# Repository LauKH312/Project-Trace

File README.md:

# Project Trace
Multimeter-oscilloscope made for the DTU Bsc. Introductory Project

## Project Structure
```txt
project-root/
│
├── hardware/              # KiCad
│   ├── boards/
│   │   └── main_board/
│   ├── libraries/
│   │   ├── symbols/
│   │   ├── footprints/
│   │   └── 3dmodels/
│   └── fabrication/
│
├── firmware/
│   └── trace-cube/
│
├── docs/
│   ├── architecture/
│   ├── hardware/
│   ├── firmware/
│   ├── manufacturing/
│   └── user_manual/
│
├── scripts/               # build + automation tools
├── tools/                 # dev utilities (flashers, converters)
│
├── .gitignore
├── README.md
└── VERSION
```

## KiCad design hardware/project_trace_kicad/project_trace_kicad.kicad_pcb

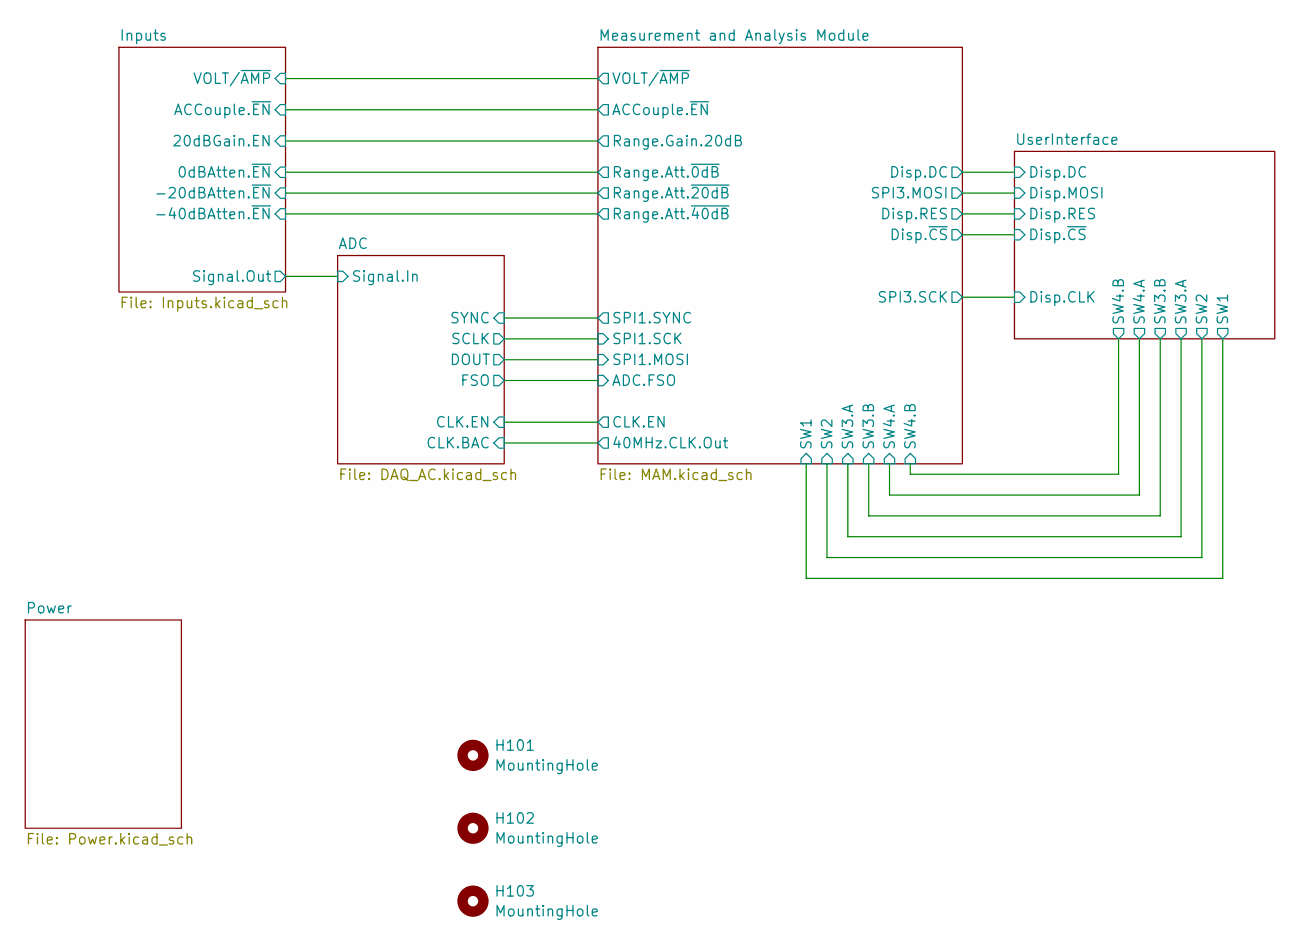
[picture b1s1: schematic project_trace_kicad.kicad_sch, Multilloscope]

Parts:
H101, H102, H103: MountingHole; MountingHole_4.3mm_M4_DIN965; DigikeyPN N/A

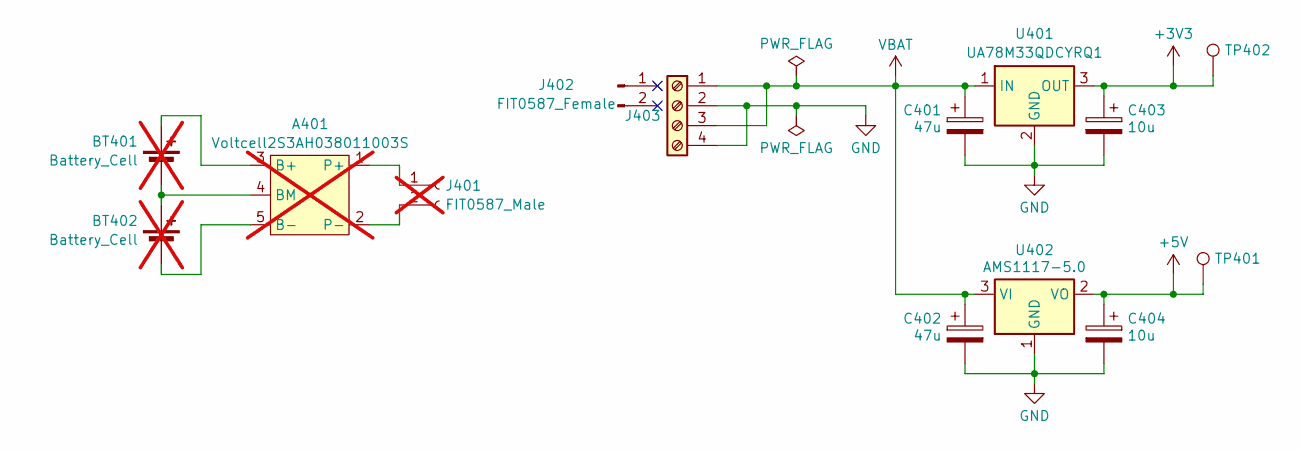
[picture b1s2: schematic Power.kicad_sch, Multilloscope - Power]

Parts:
A401: Voltcell2S3AH038011003S; DigikeyPN N/A; not fitted
BT401, BT402: Battery_Cell; DigikeyPN N/A; not fitted
C401, C402: 47u; CP_Radial_D6.3mm_P2.50mm; DigikeyPN N/A
C403, C404: 10u; CP_Radial_D6.3mm_P2.50mm; DigikeyPN N/A
J401: FIT0587_Male; DigikeyPN N/A; not fitted
J402: FIT0587_Female; DigikeyPN N/A
J403: Screw_Terminal_01x04; 691210910004; DigikeyPN 732-691210910004-ND
TP401, TP402: TestPoint; TestPoint_Pad_1.5x1.5mm; DigikeyPN N/A
U401: UA78M33QDCYRQ1; SOT-223-3_TabPin2; DigikeyPN 296-13424-1-ND
U402: AMS1117-5.0; SOT-223-3_TabPin2; DigikeyPN 5272-AMS1117-5.0CT-ND

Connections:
+3V3: C403.1, TP402.1 (1_1), U401.3 (OUT); also elsewhere on the board
+5V: C404.1, TP401.1 (1_1), U402.2 (VO); also elsewhere on the board
GND: C401.2, C402.2, C403.2, C404.2, J403.2, J403.4, U401.2 (GND), U402.1 (GND); also elsewhere on the board
unnamed: A401.1 (P+), J401.1
unnamed: A401.2 (P-), J401.2
unnamed: A401.3 (B+), BT401.1 (+)
unnamed: A401.4 (BM), BT401.2 (-), BT402.1 (+)
unnamed: A401.5 (B-), BT402.2 (-)
VBAT: C401.1, C402.1, J403.1, J403.3, U401.1 (IN), U402.3 (VI)

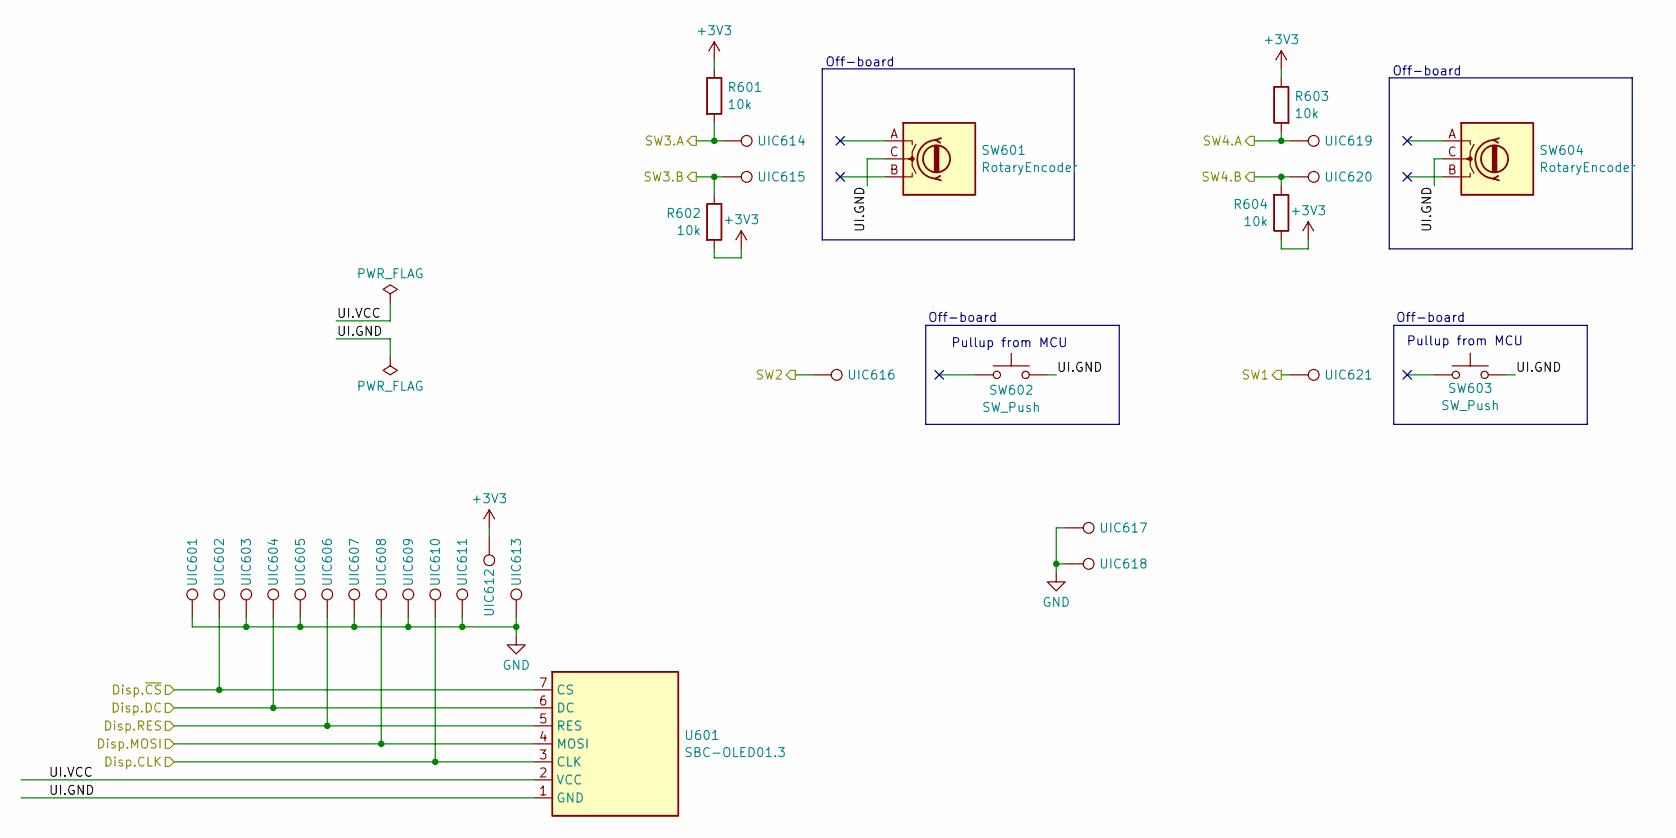
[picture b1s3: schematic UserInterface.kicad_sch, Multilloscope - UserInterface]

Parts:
R601, R602, R603, R604: 10k; R_0603_1608Metric_Pad0.98x0.95mm_HandSolder; DigikeyPN YAG1236CT-ND
SW601, SW604: RotaryEncoder; DigikeyPN N/A
SW602, SW603: SW_Push; DigikeyPN N/A
U601: SBC-OLED01.3; DigikeyPN N/A
UIC601, UIC602, UIC603, UIC604, UIC605, UIC606, UIC607, UIC608, UIC609, UIC610, UIC611, UIC612, UIC613, UIC614, UIC615, UIC616, UIC617, UIC618, UIC619, UIC620, UIC621: UIconnector; TestPoint_Pad_D2.5mm; DigikeyPN N/A

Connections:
+3V3: R601.1, R602.2, R603.1, R604.1, UIC612.1 (1_1); also elsewhere on the board
/Measurement and Analysis Module/Disp.DC: U601.6 (DC), UIC604.1 (1_1); also elsewhere on the board
/Measurement and Analysis Module/Disp.RES: U601.5 (RES), UIC606.1 (1_1); also elsewhere on the board
/Measurement and Analysis Module/Disp.~CS: U601.7 (CS), UIC602.1 (1_1); also elsewhere on the board
/Measurement and Analysis Module/SPI3.MOSI: U601.4 (MOSI), UIC608.1 (1_1); also elsewhere on the board
/Measurement and Analysis Module/SPI3.SCK: U601.3 (CLK), UIC610.1 (1_1); also elsewhere on the board
/Measurement and Analysis Module/SW1: UIC621.1 (1_1); also elsewhere on the board
/Measurement and Analysis Module/SW2: UIC616.1 (1_1); also elsewhere on the board
/Measurement and Analysis Module/SW3.A: R601.2, UIC614.1 (1_1); also elsewhere on the board
/Measurement and Analysis Module/SW3.B: R602.1, UIC615.1 (1_1); also elsewhere on the board
/Measurement and Analysis Module/SW4.A: R603.2, UIC619.1 (1_1); also elsewhere on the board
/Measurement and Analysis Module/SW4.B: R604.2, UIC620.1 (1_1); also elsewhere on the board
GND: UIC601.1 (1_1), UIC603.1 (1_1), UIC605.1 (1_1), UIC607.1 (1_1), UIC609.1 (1_1), UIC611.1 (1_1), UIC613.1 (1_1), UIC617.1 (1_1), UIC618.1 (1_1); also elsewhere on the board
unnamed: SW601.C, SW602.1, SW603.2, SW604.C, U601.1 (GND)

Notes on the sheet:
Pullup from MCU
Off-board

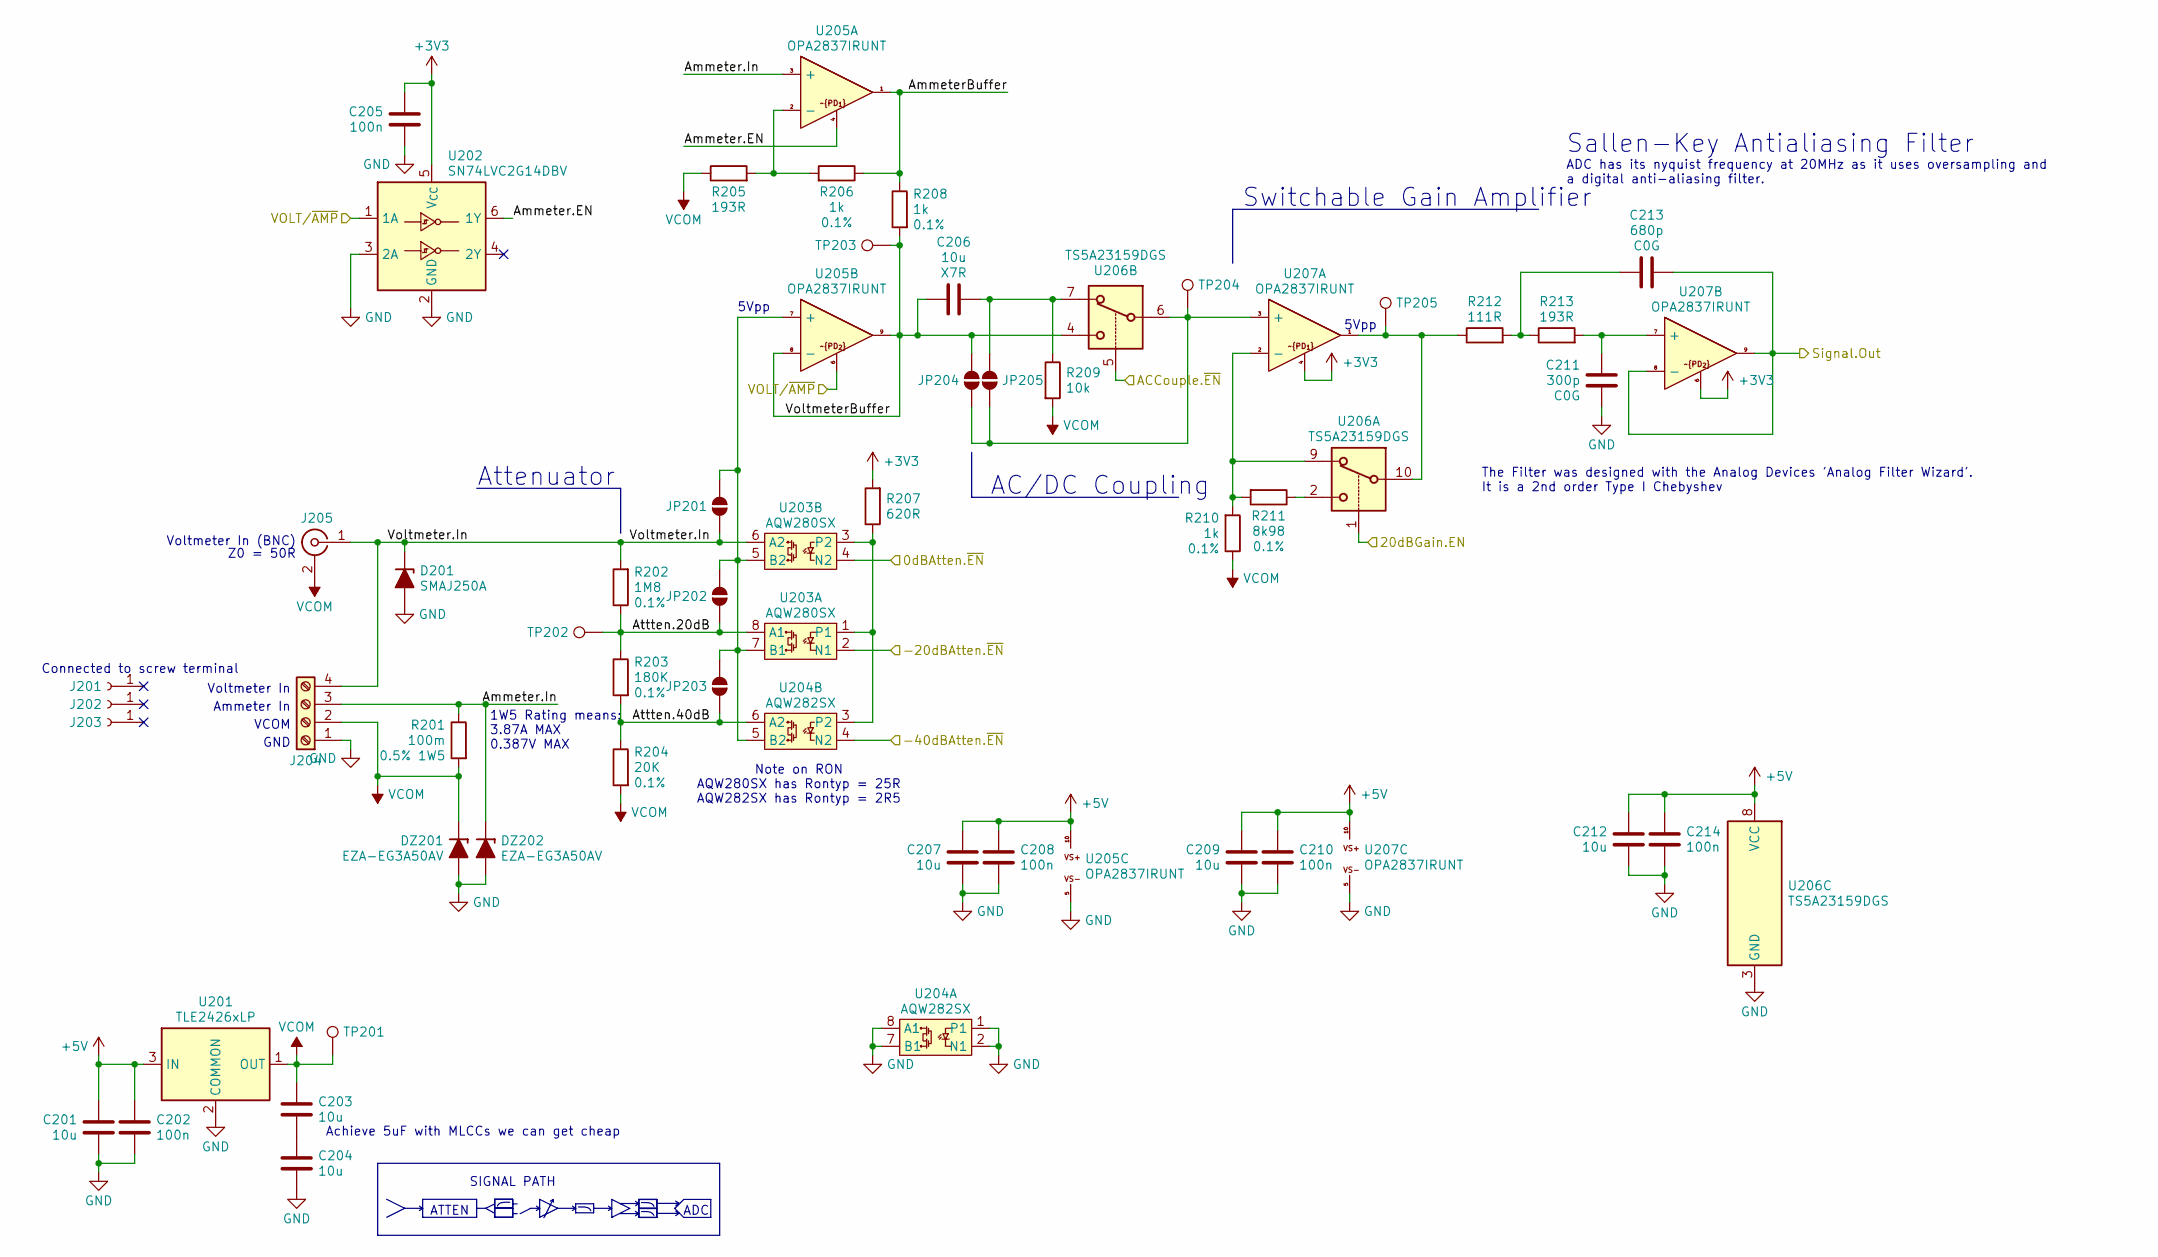
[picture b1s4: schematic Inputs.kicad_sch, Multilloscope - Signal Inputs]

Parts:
C201, C203, C204, C206, C207, C209, C212: 10u; C_0805_2012Metric_Pad1.18x1.45mm_HandSolder; DigikeyPN 490-10516-1-ND
C202, C205, C208, C210, C214: 100n; C_0603_1608Metric_Pad1.08x0.95mm_HandSolder; DigikeyPN 399-C0603C104K3RACTUCT-ND
C211: 300p; C_0603_1608Metric_Pad1.08x0.95mm_HandSolder; DigikeyPN 311-3967-1-ND
C213: 680p; C_0603_1608Metric_Pad1.08x0.95mm_HandSolder; DigikeyPN 311-1425-1-ND
D201: SMAJ250A; D_SMA_Handsoldering; DigikeyPN 13-SMAJ250A/TR13CT-ND
DZ201, DZ202: EZA-EG3A50AV; D_0603_1608Metric_Pad1.05x0.95mm_HandSolder; MouserPN 667-EZA-EG3A50AV
J201, J202, J203: Conn_01x01_Socket; DigikeyPN N/A
J204: Screw_Terminal_01x04; 691210910004; MouserPN 710-691210910004
J205: Conn_Coaxial; BNC_Female_0731385003; DigikeyPN WM14063-ND
JP201, JP202, JP203, JP204, JP205: SolderJumper_2_Open; SolderJumper-2_P1.3mm_Open_RoundedPad1.0x1.5mm; DigikeyPN N/A
R201: 100m; R_2512_6332Metric_Pad1.40x3.35mm_HandSolder; MouserPN SLW1TTER100D
R202: 1M8; R_0805_2012Metric_Pad1.20x1.40mm_HandSolder; DigikeyPN 408-2026-1-ND
R203: 180K; R_0603_1608Metric_Pad0.98x0.95mm_HandSolder; DigikeyPN YAG1548CT-ND
R204: 20K; R_0603_1608Metric_Pad0.98x0.95mm_HandSolder; DigikeyPN YAG1582CT-ND
R205, R213: 193R; R_0603_1608Metric_Pad0.98x0.95mm_HandSolder; DigikeyPN 13-RT0603DRE07193RLCT-ND
R206, R208, R210: 1k; R_0603_1608Metric_Pad0.98x0.95mm_HandSolder; DigikeyPN YAG1237CT-ND
R207: 620R; R_Axial_DIN0207_L6.3mm_D2.5mm_P10.16mm_Horizontal; DigikeyPN N/A
R209: 10k; R_0603_1608Metric_Pad0.98x0.95mm_HandSolder; DigikeyPN YAG1236CT-ND
R211: 8k98; R_0603_1608Metric_Pad0.98x0.95mm_HandSolder; DigikeyPN 13-RT0603BRD078K98LCT-ND
R212: 111R; R_0603_1608Metric_Pad0.98x0.95mm_HandSolder; DigikeyPN 2019-RN73R1JTTD1110B25CT-ND
TP201, TP202, TP203, TP204, TP205: TestPoint; TestPoint_Pad_1.5x1.5mm; DigikeyPN N/A
U201: TLE2426xLP; TO-92_Inline_Wide; DigikeyPN 296-TLE2426CLPRCT-ND
U202: SN74LVC2G14DBV; SOT-23-6_Handsoldering; DigikeyPN 296-13010-1-ND
U203: AQW280SX; AQW282SX; MouserPN 769-AQW280SX
U204: AQW282SX; DigikeyPN 255-AQW282SXCT-ND
U205, U207: OPA2837IRUNT; OPA2837IRUNT-Handsolder; DigikeyPN 296-53042-1-ND
U206: TS5A23159DGS; TSSOP-10_3x3mm_P0.5mm; DigikeyPN 296-18598-1-ND

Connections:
+3V3: C205.1, R207.2, U202.5 (V_{CC}), U207.4, U207.6; also elsewhere on the board
+5V: C201.2, C202.1, C207.2, C208.1, C209.2, C210.1, C212.2, C214.1, U201.3 (IN), U205.10, U206.8 (VCC), U207.10; also elsewhere on the board
/ADC/Signal.In: C213.2, U207.8 (-), U207.9; also elsewhere on the board
/Inputs/0dBAtten.~EN: U203.4 (N2); also elsewhere on the board
/Inputs/20dBGain.EN: U206.1; also elsewhere on the board
/Inputs/-20dBAtten.~EN: U203.2 (N1); also elsewhere on the board
/Inputs/-40dBAtten.~EN: U204.4 (N2); also elsewhere on the board
/Inputs/ACCouple.~EN: U206.5; also elsewhere on the board
/Inputs/Ammeter.EN: U202.6 (1Y), U205.4
/Inputs/Ammeter.In: DZ202.1 (K), J204.3, R201.1, U205.3 (+)
/Inputs/AmmeterBuffer: R206.1, R208.1, U205.1
/Inputs/Attten.20dB: JP202.1 (A), R202.1, R203.1, TP202.1 (1_1), U203.8 (A1)
/Inputs/Attten.40dB: JP203.1 (A), R203.2, R204.1, U204.6 (A2)
/Inputs/VOLT/~AMP: U202.1 (1A), U205.6; also elsewhere on the board
/Inputs/Voltmeter.In: D201.1 (K), J204.4, J205.1 (In), JP201.1 (A), R202.2, U203.6 (A2)
/Inputs/VoltmeterBuffer: C206.2, JP204.1 (A), R208.2, TP203.1 (1_1), U205.8 (-), U205.9, U206.4
GND: C201.1, C202.2, C204.1, C205.2, C207.1, C208.2, C209.1, C210.2, C211.1, C212.1, C214.2, D201.2 (A), DZ201.2 (A), DZ202.2 (A), J204.1, U201.2 (COMMON), U202.2 (GND), U202.3 (2A), U204.1, U204.2 (N1), U204.7 (B1), U204.8 (A1), U205.5, U206.3 (GND), U207.5; also elsewhere on the board
unnamed: C203.1, C204.2
unnamed: C213.1, R212.2, R213.1
unnamed: JP201.2 (B), JP202.2 (B), JP203.2 (B), U203.5 (B2), U203.7 (B1), U204.5 (B2), U205.7 (+)
unnamed: JP204.2 (B), JP205.2 (B), TP204.1 (1_1), U206.6, U207.3 (+)
unnamed: C206.1, JP205.1 (A), R209.1, U206.7
unnamed: R211.1, U206.2
unnamed: R212.1, TP205.1 (1_1), U206.10, U207.1
unnamed: R207.1, U203.1, U203.3 (P2), U204.3 (P2)
unnamed: R205.2, R206.2, U205.2 (-)
unnamed: R210.2, R211.2, U206.9, U207.2 (-)
unnamed: C211.2, R213.2, U207.7 (+)
VCOM: C203.2, DZ201.1 (K), J204.2, J205.2 (Ext), R201.2, R204.2, R205.1, R209.2, R210.1, TP201.1 (1_1), U201.1 (OUT); also elsewhere on the board

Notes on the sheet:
ADC has its nyquist frequency at 20MHz as it uses oversampling and a digital anti-aliasing filter.
GND
Voltmeter In
Attenuator
VCOM
The Filter was designed with the Analog Devices 'Analog Filter Wizard'. It is a 2nd order Type I Chebyshev
Achieve 5uF with MLCCs we can get cheap
Note on RON AQW280SX has Rontyp = 25R AQW282SX has Rontyp = 2R5
Z0 = 50R
ADC
ATTEN
5Vpp
1W5 Rating means: 3.87A MAX 0.387V MAX
Ammeter In
AC/DC Coupling
Switchable Gain Amplifier
SIGNAL PATH
Sallen-Key Antialiasing Filter
Connected to screw terminal
Voltmeter In (BNC)

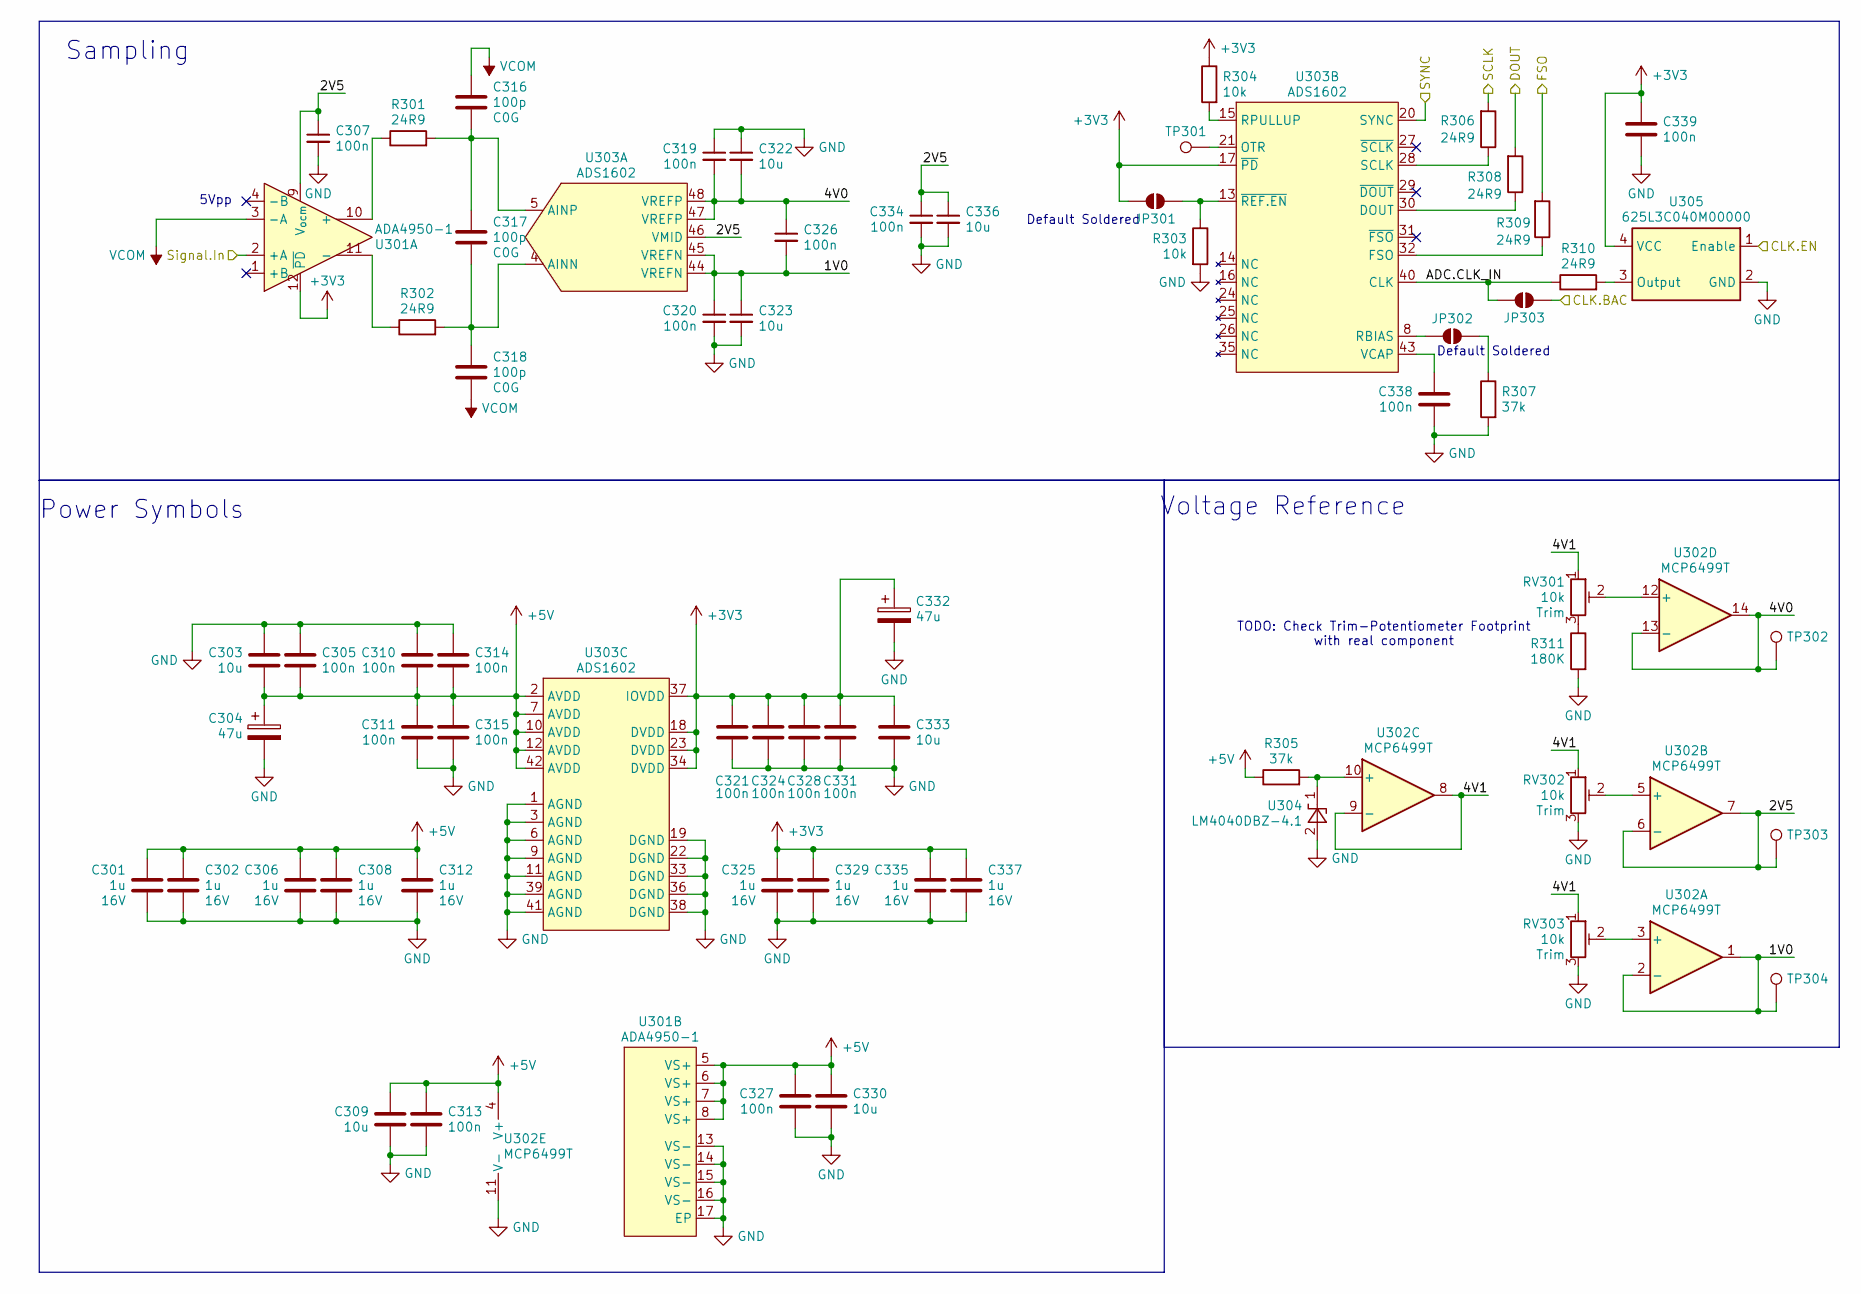
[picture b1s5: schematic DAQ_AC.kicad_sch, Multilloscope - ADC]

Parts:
C301, C302, C306, C308, C312, C325, C329, C335, C337: 1u; C_0603_1608Metric_Pad1.08x0.95mm_HandSolder; DigikeyPN 399-C0603C105K4RACTUCT-ND
C303, C309, C322, C323, C330, C333, C336: 10u; C_0805_2012Metric_Pad1.18x1.45mm_HandSolder; DigikeyPN 490-10516-1-ND
C304, C332: 47u; CP_Radial_D6.3mm_P2.50mm; DigikeyPN N/A
C305, C307, C310, C311, C313, C314, C315, C319, C320, C321, C324, C326, C327, C328, C331, C334, C338, C339: 100n; C_0603_1608Metric_Pad1.08x0.95mm_HandSolder; DigikeyPN 399-C0603C104K3RACTUCT-ND
C316, C317, C318: 100p; C_0603_1608Metric_Pad1.08x0.95mm_HandSolder; DigikeyPN 311-1069-1-ND
JP301, JP302, JP303: SolderJumper_2_Open; SolderJumper-2_P1.3mm_Open_RoundedPad1.0x1.5mm; DigikeyPN N/A
R301, R302, R306, R308, R309, R310: 24R9; R_0603_1608Metric_Pad0.98x0.95mm_HandSolder; DigikeyPN YAG4511CT-ND
R303, R304: 10k; R_0603_1608Metric_Pad0.98x0.95mm_HandSolder; DigikeyPN YAG1236CT-ND
R305, R307: 37k; R_0603_1608Metric_Pad0.98x0.95mm_HandSolder; DigikeyPN 2019-RN73R1JTTD3702F100CT-ND
R311: 180K; R_0603_1608Metric_Pad0.98x0.95mm_HandSolder; DigikeyPN YAG1548CT-ND
RV301, RV302, RV303: 10k; Potentiometer_Bourns_3266W_Vertical; DigikeyPN N/A
TP301, TP302, TP303, TP304: TestPoint; TestPoint_Pad_1.5x1.5mm; DigikeyPN N/A
U301: ADA4950-1; ADA4950-QFN-16_EP_3.1x3.1_Pitch0.5mm; DigikeyPN 505-ADA4950-1YCPZ-R7CT-ND
U302: MCP6499T; SOIC-14_3.9x8.7mm_P1.27mm_Handsolder; DigikeyPN 150-MCP6499T-E/SLCT-ND
U303: ADS1602; LQFP-48_7x7_Pitch0.5mm - PFB0048A; DigikeyPN 296-17890-1-ND
U304: LM4040DBZ-4.1; SOT-23_Handsoldering; DigikeyPN 576-2568-1-ND
U305: 625L3C040M00000; IC_625L3C040M00000_CTS-M; DigikeyPN 110-625L3C040M00000CT-ND

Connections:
+3V3: C321.2, C324.2, C325.2, C328.2, C329.2, C331.2, C332.1, C333.2, C335.2, C337.2, C339.2, JP301.2 (B), R304.1, U301.12 (~PD), U303.17 (~PD), U303.18 (DVDD), U303.23 (DVDD), U303.34 (DVDD), U303.37 (IOVDD), U305.4 (VCC); also elsewhere on the board
+5V: C301.2, C302.2, C303.1, C304.1, C305.1, C306.2, C308.2, C309.2, C310.1, C311.2, C312.2, C313.2, C314.1, C315.2, C327.2, C330.2, R305.1, U301.5 (VS+), U301.6 (VS+), U301.7 (VS+), U301.8 (VS+), U302.4 (V+), U303.2 (AVDD), U303.7 (AVDD), U303.10 (AVDD), U303.12 (AVDD), U303.42 (AVDD); also elsewhere on the board
/ADC/1V0: C320.1, C323.1, C326.2, TP304.1 (1_1), U302.1, U302.2 (-), U303.44 (VREFN), U303.45 (VREFN)
/ADC/2V5: C307.1, C334.1, C336.1, TP303.1 (1_1), U301.9 (V_{ocm}), U302.6 (-), U302.7, U303.46 (VMID)
/ADC/4V0: C319.2, C322.2, C326.1, TP302.1 (1_1), U302.13 (-), U302.14, U303.47 (VREFP), U303.48 (VREFP)
/ADC/4V1: RV301.1, RV302.1, RV303.1, U302.8, U302.9 (-)
/ADC/ADC.CLK_IN: JP303.2 (B), R310.1, U303.40 (CLK)
/ADC/CLK.BAC: JP303.1 (A); also elsewhere on the board
/ADC/CLK.EN: U305.1 (Enable); also elsewhere on the board
/ADC/DOUT: R308.2; also elsewhere on the board
/ADC/FSO: R309.2; also elsewhere on the board
/ADC/SCLK: R306.2; also elsewhere on the board
/ADC/SYNC: U303.20 (SYNC); also elsewhere on the board
/ADC/Signal.In: U301.2 (+A); also elsewhere on the board
GND: C301.1, C302.1, C303.2, C304.2, C305.2, C306.1, C307.2, C308.1, C309.1, C310.2, C311.1, C312.1, C313.1, C314.2, C315.1, C319.1, C320.2, C321.1, C322.1, C323.2, C324.1, C325.1, C327.1, C328.1, C329.1, C330.1, C331.1, C332.2, C333.1, C334.2, C335.1, C336.2, C337.1, C338.1, C339.1, R303.2, R307.2, R311.2, RV302.3, RV303.3, U301.13 (VS-), U301.14 (VS-), U301.15 (VS-), U301.16 (VS-), U301.17 (EP), U302.11 (V-), U303.1 (AGND), U303.3 (AGND), U303.6 (AGND), U303.9 (AGND), U303.11 (AGND), U303.19 (DGND), U303.22 (DGND), U303.33 (DGND), U303.36 (DGND), U303.38 (DGND), U303.39 (AGND), U303.41 (AGND), U304.2 (A), U305.2 (GND); also elsewhere on the board
unnamed: JP301.1 (A), R303.1, U303.13 (~REF.EN)
unnamed: JP302.1 (A), R307.1
unnamed: JP302.2 (B), U303.8 (RBIAS)
unnamed: R311.1, RV301.3
unnamed: R301.1, U301.10 (+)
unnamed: R302.1, U301.11 (-)
unnamed: RV303.2, U302.3 (+)
unnamed: RV302.2, U302.5 (+)
unnamed: R305.2, U302.10 (+), U304.1 (K)
unnamed: RV301.2, U302.12 (+)
unnamed: C317.2, C318.1, R302.2, U303.4 (AINN)
unnamed: C316.2, C317.1, R301.2, U303.5 (AINP)
unnamed: R308.1, U303.30 (DOUT)
unnamed: R309.1, U303.32 (FSO)
unnamed: TP301.1 (1_1), U303.21 (OTR)
unnamed: R304.2, U303.15 (RPULLUP)
unnamed: R306.1, U303.28 (SCLK)
unnamed: C338.2, U303.43 (VCAP)
unnamed: R310.2, U305.3 (Output)
VCOM: C316.1, C318.2, U301.3 (-A); also elsewhere on the board

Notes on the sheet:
Power Symbols
5Vpp
Default Soldered
Voltage Reference
TODO: Check Trim-Potentiometer Footprint with real component
Sampling

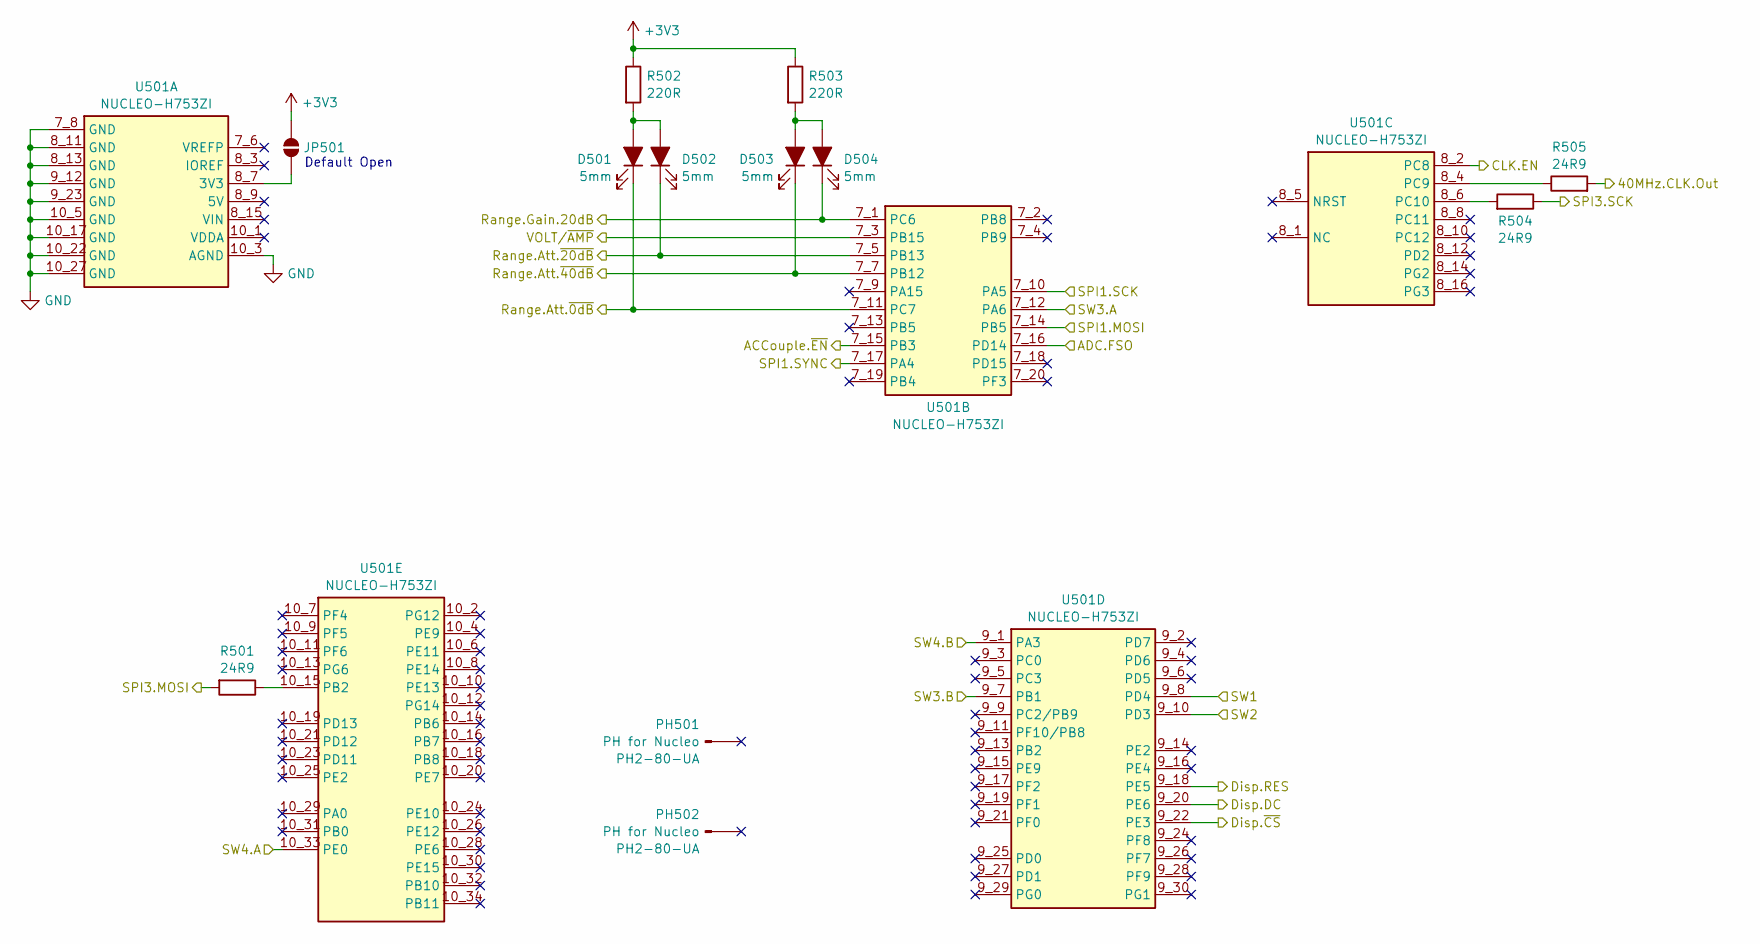
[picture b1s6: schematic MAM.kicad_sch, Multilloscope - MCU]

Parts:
D501, D502, D503, D504: 5mm; LED_D5.0mm; DigikeyPN N/A
JP501: SolderJumper_2_Open; SolderJumper-2_P1.3mm_Open_RoundedPad1.0x1.5mm; DigikeyPN N/A
PH501, PH502: PH for Nucleo; DigikeyPN 2057-PH2-80-UA-ND
R501, R504, R505: 24R9; R_0603_1608Metric_Pad0.98x0.95mm_HandSolder; DigikeyPN YAG4511CT-ND
R502, R503: 220R; R_Axial_DIN0207_L6.3mm_D2.5mm_P10.16mm_Horizontal; DigikeyPN N/A
U501: NUCLEO-H753ZI; MODULE_NUCLEO-H753ZI; DigikeyPN N/A

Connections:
+3V3: JP501.1 (A), R502.1, R503.1; also elsewhere on the board
/ADC/CLK.BAC: R505.2; also elsewhere on the board
/ADC/CLK.EN: U501.8_2 (PC8); also elsewhere on the board
/ADC/DOUT: U501.7_14 (PB5); also elsewhere on the board
/ADC/FSO: U501.7_16 (PD14); also elsewhere on the board
/ADC/SCLK: U501.7_10 (PA5); also elsewhere on the board
/ADC/SYNC: U501.7_17 (PA4); also elsewhere on the board
/Inputs/0dBAtten.~EN: D501.1 (K), U501.7_11 (PC7); also elsewhere on the board
/Inputs/20dBGain.EN: D504.1 (K), U501.7_1 (PC6); also elsewhere on the board
/Inputs/-20dBAtten.~EN: D502.1 (K), U501.7_5 (PB13); also elsewhere on the board
/Inputs/-40dBAtten.~EN: D503.1 (K), U501.7_7 (PB12); also elsewhere on the board
/Inputs/ACCouple.~EN: U501.7_15 (PB3); also elsewhere on the board
/Inputs/VOLT/~AMP: U501.7_3 (PB15); also elsewhere on the board
/Measurement and Analysis Module/Disp.DC: U501.9_20 (PE6); also elsewhere on the board
/Measurement and Analysis Module/Disp.RES: U501.9_18 (PE5); also elsewhere on the board
/Measurement and Analysis Module/Disp.~CS: U501.9_22 (PE3); also elsewhere on the board
/Measurement and Analysis Module/SPI3.MOSI: R501.2; also elsewhere on the board
/Measurement and Analysis Module/SPI3.SCK: R504.1; also elsewhere on the board
/Measurement and Analysis Module/SW1: U501.9_8 (PD4); also elsewhere on the board
/Measurement and Analysis Module/SW2: U501.9_10 (PD3); also elsewhere on the board
/Measurement and Analysis Module/SW3.A: U501.7_12 (PA6); also elsewhere on the board
/Measurement and Analysis Module/SW3.B: U501.9_7 (PB1); also elsewhere on the board
/Measurement and Analysis Module/SW4.A: U501.10_33 (PE0); also elsewhere on the board
/Measurement and Analysis Module/SW4.B: U501.9_1 (PA3); also elsewhere on the board
GND: U501.7_8 (GND), U501.8_11 (GND), U501.8_13 (GND), U501.9_12 (GND), U501.9_23 (GND), U501.10_3 (AGND), U501.10_5 (GND), U501.10_17 (GND), U501.10_22 (GND), U501.10_27 (GND); also elsewhere on the board
unnamed: D501.2 (A), D502.2 (A), R502.2
unnamed: D503.2 (A), D504.2 (A), R503.2
unnamed: JP501.2 (B), U501.8_7 (3V3)
unnamed: R505.1, U501.8_4 (PC9)
unnamed: R504.2, U501.8_6 (PC10)
unnamed: R501.1, U501.10_15 (PB2)

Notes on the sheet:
Default Open

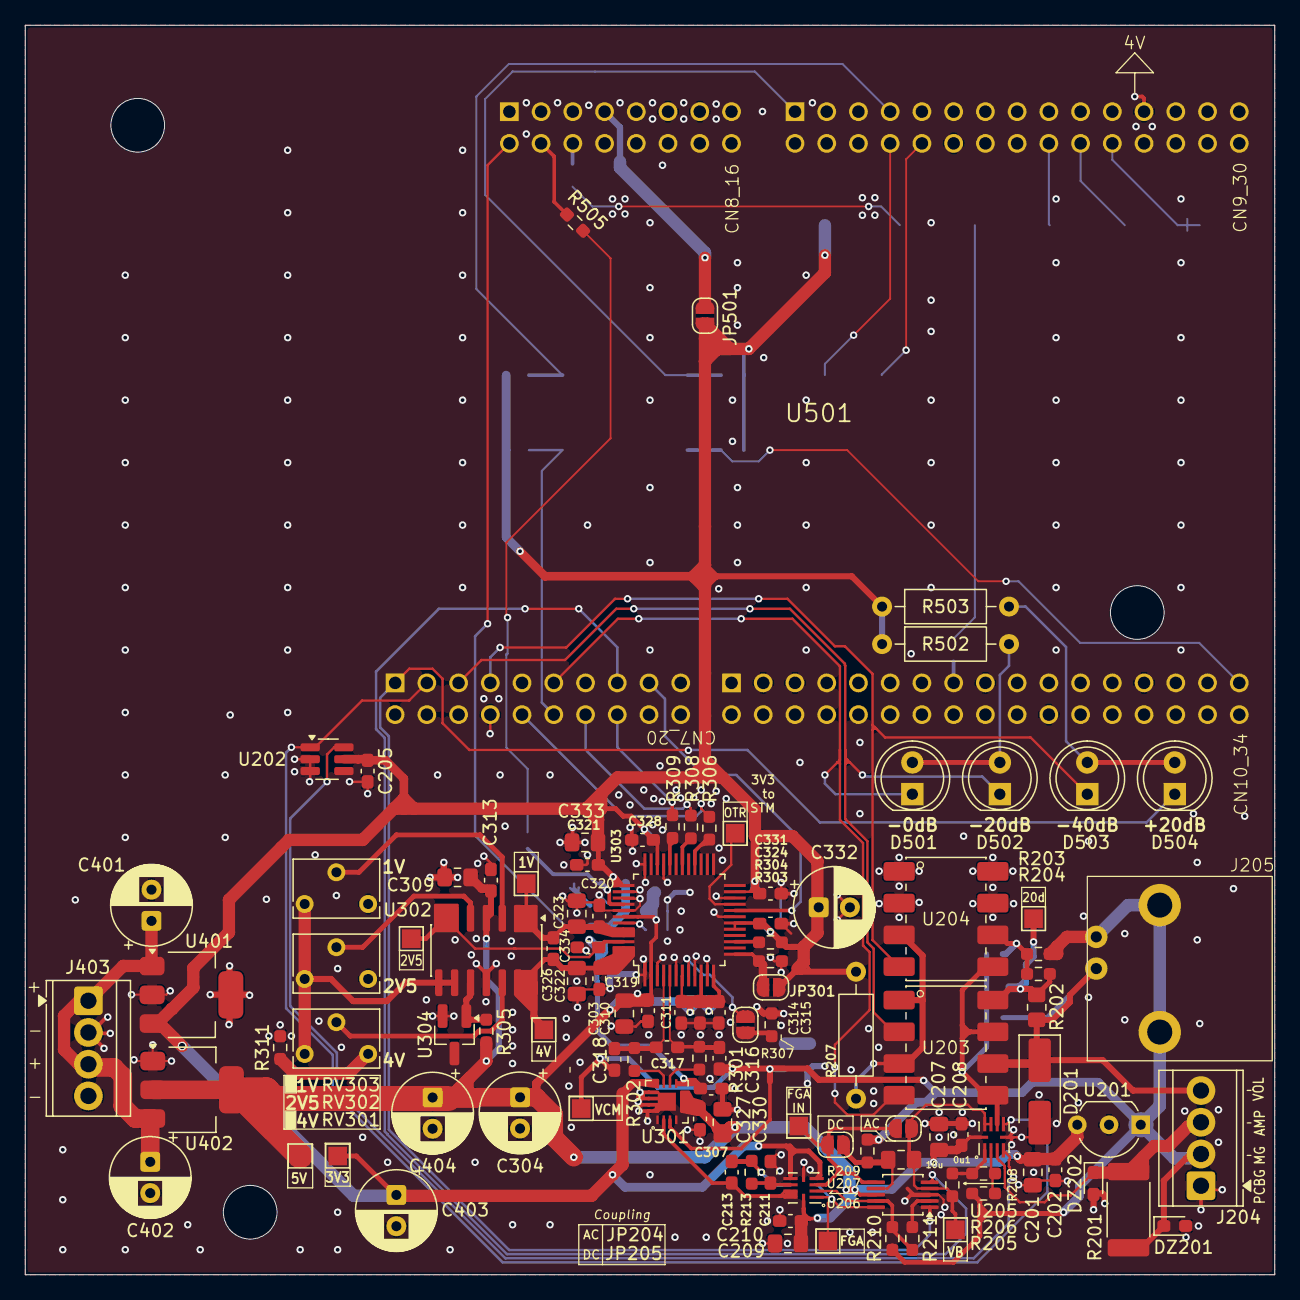
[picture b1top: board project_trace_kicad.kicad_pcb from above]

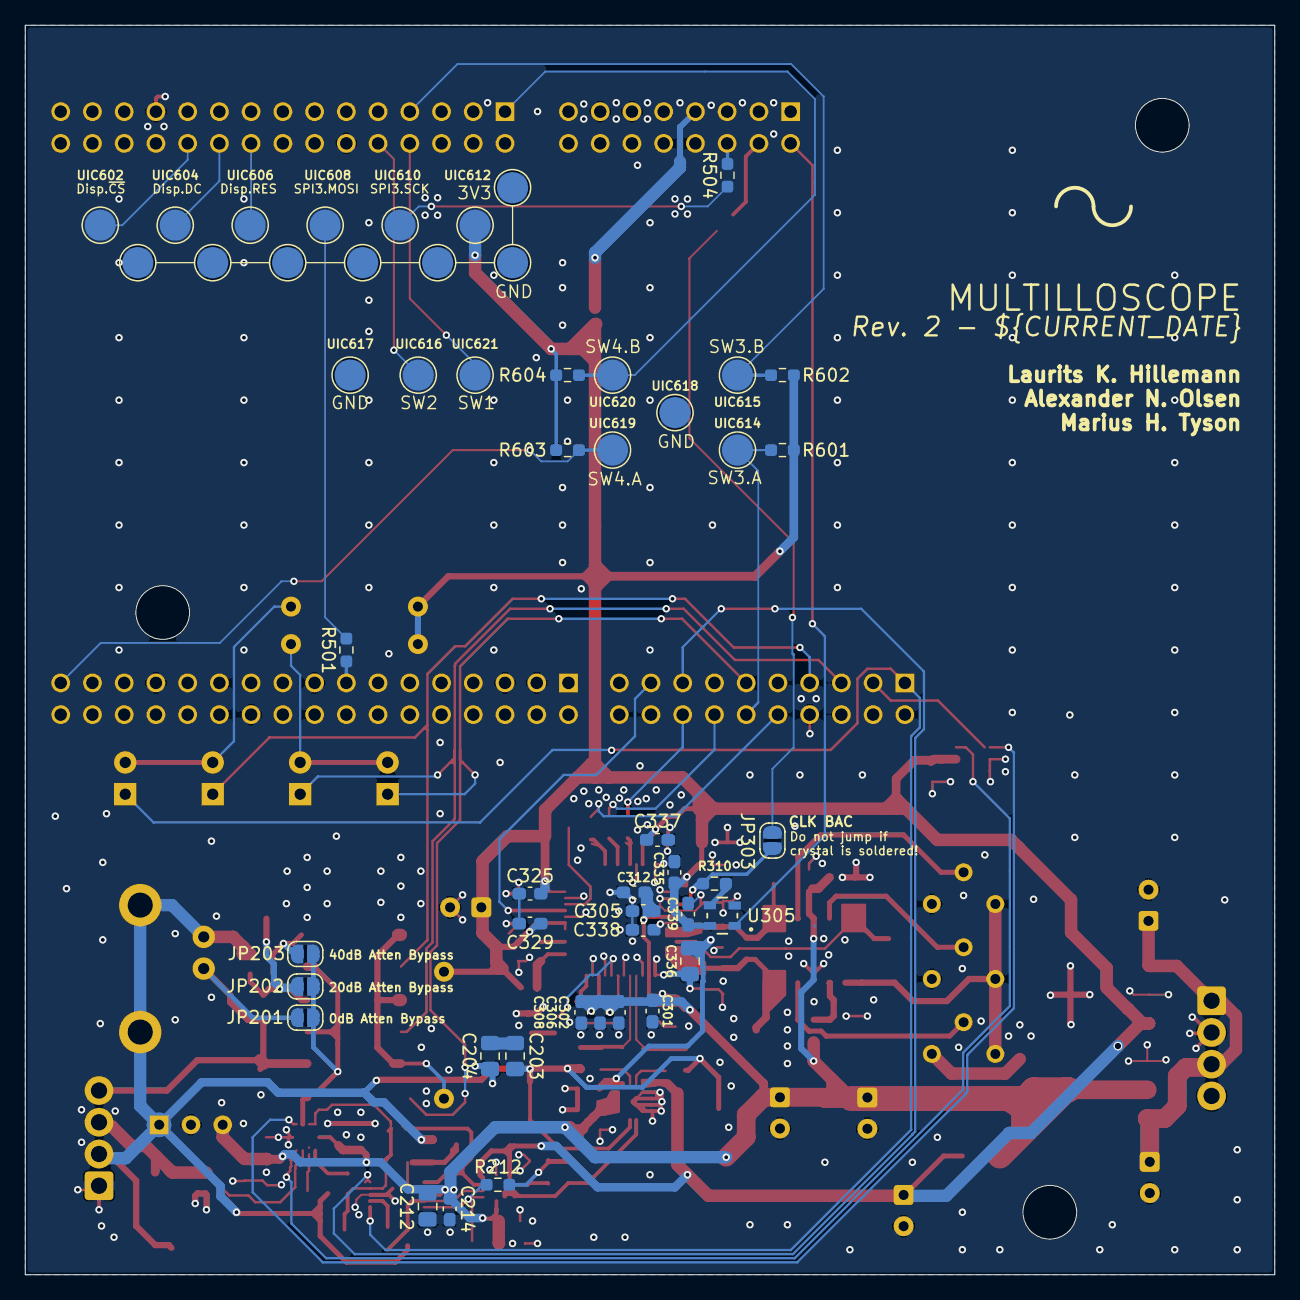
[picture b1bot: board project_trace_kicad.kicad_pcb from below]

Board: 4 copper layers, 100.0 x 100.0 mm, 162 parts (51 on the bottom side), 77 nets.
